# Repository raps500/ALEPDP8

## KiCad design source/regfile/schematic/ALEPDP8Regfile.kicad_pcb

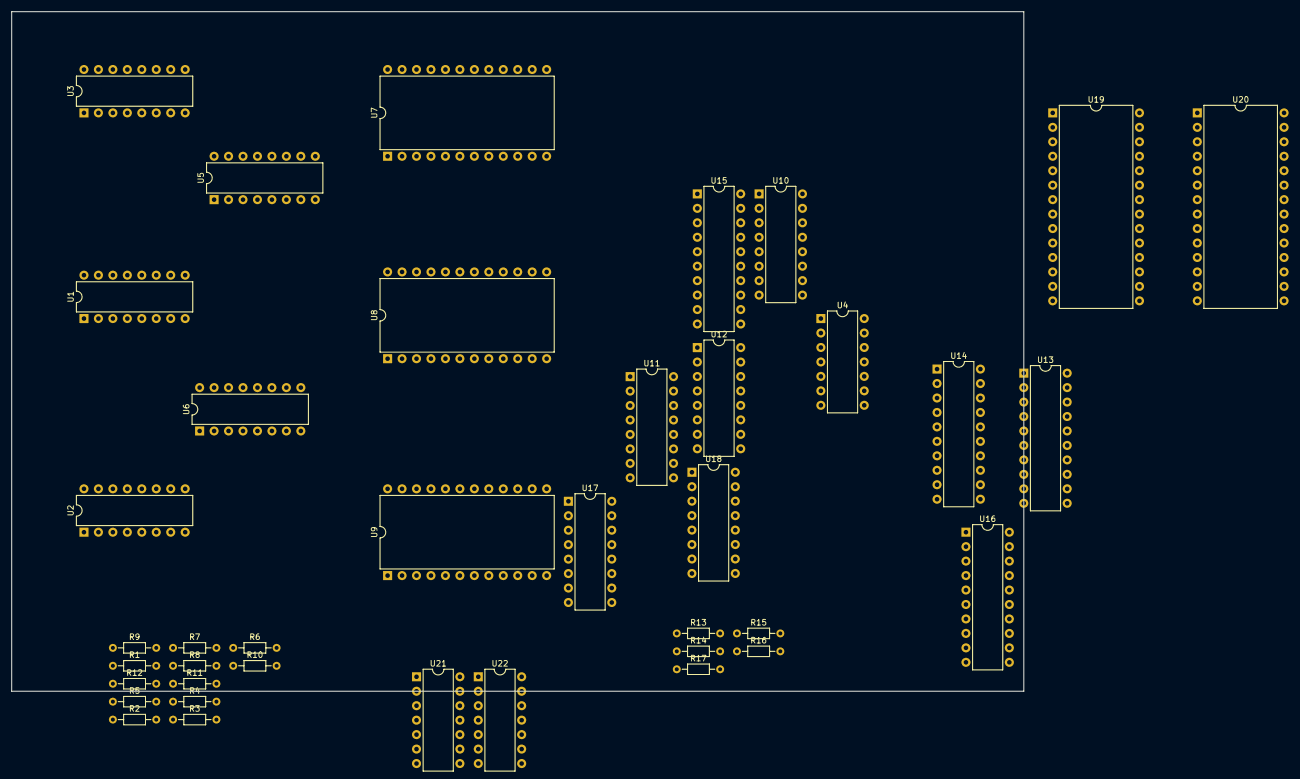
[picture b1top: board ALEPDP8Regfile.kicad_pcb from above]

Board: 2 copper layers, 177.8 x 119.4 mm, 39 parts (0 on the bottom side), 97 nets, no tracks yet.

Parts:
R1, R2, R3, R4, R5, R6, R7, R8, R9, R10, R11, R12, R13, R14, R15, R16, R17: 1 k; R_Axial_DIN0204_L3.6mm_D1.6mm_P7.62mm_Horizontal
U1, U2, U3: 74LS670; DIP-16_W7.62mm
U4, U21: 74LS125; DIP-14_W7.62mm
U5, U6, U17, U18: 74LS174; DIP-16_W7.62mm
U7, U8, U9: 74LS181; DIP-24_W15.24mm
U10, U11, U12: 74LS194; DIP-16_W7.62mm
U13: 74LS541; DIP-20_W7.62mm
U14, U15, U16: 74LS244; DIP-20_W7.62mm
U19, U20: CY62256-70PC; DIP-28_W15.24mm
U22: 74LS74; DIP-14_W7.62mm

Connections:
+5V: U1.16 (VCC), U2.16 (VCC), U3.16 (VCC), U5.16 (VCC), U6.16 (VCC), U7.24 (VCC), U8.24 (VCC), U9.24 (VCC), U10.16 (VCC), U11.16 (VCC), U12.16 (VCC), U14.20 (VCC), U15.20 (VCC), U16.20 (VCC), U17.1 (~Mr), U17.16 (VCC), U18.1 (~Mr), U18.16 (VCC), U19.28 (VCC), U20.28 (VCC)
/IBUS0: U3.15 (D1), U5.3 (D0), U13.18 (Y0), U14.2 (I0a), U14.11 (I0b), U17.3 (D0)
/IBUS1: U3.1 (D2), U5.4 (D1), U13.17 (Y1), U14.4 (I1a), U14.13 (I1b), U17.4 (D1)
/IBUS2: U3.2 (D3), U5.6 (D2), U13.16 (Y2), U14.6 (I2a), U14.15 (I2b), U17.6 (D2)
/IBUS3: U3.3 (D4), U5.11 (D3), U13.15 (Y3), U14.8 (I3a), U14.17 (I3b), U17.11 (D3)
/IBUS4: U1.15 (D1), U5.13 (D4), U13.14 (Y4), U15.2 (I0a), U15.11 (I0b), U17.13 (D4)
/IBUS5: U1.1 (D2), U5.14 (D5), U13.13 (Y5), U15.4 (I1a), U15.13 (I1b), U17.14 (D5)
/IBUS6: U1.2 (D3), U6.3 (D0), U13.12 (Y6), U15.6 (I2a), U15.15 (I2b)
/IBUS7: U1.3 (D4), U6.4 (D1), U13.11 (Y7), U15.8 (I3a), U15.17 (I3b), U21.12
/IBUS8: U2.15 (D1), U4.3, U6.6 (D2), U16.2 (I0a), U16.11 (I0b)
/IBUS9: U2.1 (D2), U4.6, U6.11 (D3), U16.4 (I1a), U16.13 (I1b)
/IBUS10: U2.2 (D3), U4.8, U6.13 (D4), U16.6 (I2a), U16.15 (I2b)
/IBUS11: U2.3 (D4), U4.11, U6.14 (D5), U16.8 (I3a), U16.17 (I3b)
GND: R1.2, R2.2, R3.2, R4.2, R5.2, R6.2, R7.2, R8.2, R9.2, R10.2, R11.2, R12.2, R13.2, R14.2, R15.2, R16.2, R17.2, U1.8 (GND), U2.8 (GND), U3.8 (GND), U5.8 (GND), U6.8 (GND), U7.12 (GND), U8.12 (GND), U9.12 (GND), U10.8 (GND), U11.8 (GND), U12.8 (GND), U14.10 (GND), U15.10 (GND), U16.10 (GND), U17.8 (GND), U18.8 (GND), U19.14 (GND), U20.14 (GND)
unnamed: R1.1, U3.6 (Q4), U7.19 (A3)
unnamed: R2.1, U2.6 (Q4), U9.19 (A3)
unnamed: R3.1, U1.6 (Q4), U8.19 (A3)
unnamed: R4.1, U3.7 (Q3), U7.21 (A2)
unnamed: R5.1, U2.7 (Q3), U9.21 (A2)
unnamed: R6.1, U1.7 (Q3), U8.21 (A2)
unnamed: R7.1, U3.9 (Q2), U7.23 (A1)
unnamed: R8.1, U2.9 (Q2), U9.23 (A1)
unnamed: R9.1, U1.9 (Q2), U8.23 (A1)
unnamed: R10.1, U3.10 (Q1), U7.2 (A0)
unnamed: R11.1, U2.10 (Q1), U9.2 (A0)
unnamed: R12.1, U1.10 (Q1), U8.2 (A0)
unnamed: U1.4 (Rb), U2.4 (Rb), U3.4 (Rb)
unnamed: U1.5 (Ra), U2.5 (Ra), U3.5 (Ra)
unnamed: U1.11 (~Er), U2.11 (~Er), U3.11 (~Er)
unnamed: U1.12 (~Ew), U2.12 (~Ew), U3.12 (~Ew)
unnamed: U1.13 (Wb), U2.13 (Wb), U3.13 (Wb)
unnamed: U1.14 (Wa), U2.14 (Wa), U3.14 (Wa)
unnamed: U5.2 (Q0), U7.1 (B0)
unnamed: U5.5 (Q1), U7.22 (B1)
unnamed: U5.7 (Q2), U7.20 (B2)
unnamed: U5.10 (Q3), U7.18 (B3)
unnamed: U5.12 (Q4), U8.1 (B0)
unnamed: U5.15 (Q5), U8.22 (B1)
unnamed: U6.2 (Q0), U8.20 (B2)
unnamed: U6.5 (Q1), U8.18 (B3)
unnamed: U6.7 (Q2), U9.1 (B0)
unnamed: U6.10 (Q3), U9.22 (B1)
unnamed: U6.12 (Q4), U9.20 (B2)
unnamed: U6.15 (Q5), U9.18 (B3)
unnamed: U7.3 (S3), U8.3 (S3), U9.3 (S3)
unnamed: U7.4 (S2), U8.4 (S2), U9.4 (S2)
unnamed: U7.5 (S1), U8.5 (S1), U9.5 (S1)
unnamed: U7.6 (S0), U8.6 (S0), U9.6 (S0)
unnamed: U7.8 (M), U8.8 (M), U9.8 (M)
unnamed: U7.16 (Cn+4), U8.7 (Cn)
unnamed: U8.16 (Cn+4), U9.7 (Cn)
unnamed: U7.9 (F0), U10.3 (P0)
unnamed: U7.10 (F1), U10.4 (P1)
unnamed: U7.11 (F2), U10.5 (P2)
unnamed: U7.13 (F3), U10.6 (P3)
unnamed: U10.12 (Q3), U11.7 (Dsl), U13.5 (A3)
unnamed: U10.13 (Q2), U13.4 (A2)
unnamed: U10.14 (Q1), U13.3 (A1)
unnamed: U10.15 (Q0), U13.2 (A0), U21.5
unnamed: U4.2, U11.2 (Dsr), U12.15 (Q0)
unnamed: U8.9 (F0), U11.3 (P0)
unnamed: U8.10 (F1), U11.4 (P1)
unnamed: U8.11 (F2), U11.5 (P2)
unnamed: U8.13 (F3), U11.6 (P3)
unnamed: U11.13 (Q2), U13.8 (A6)
unnamed: U11.14 (Q1), U13.7 (A5)
unnamed: U10.2 (Dsr), U11.15 (Q0), U13.6 (A4)
unnamed: U10.7 (Dsl), U12.2 (Dsr), U22.5 (Q)
unnamed: U9.9 (F0), U12.3 (P0)
unnamed: U9.10 (F1), U12.4 (P1)
unnamed: U9.11 (F2), U12.5 (P2)
unnamed: U9.13 (F3), U12.6 (P3)
unnamed: U11.12 (Q3), U12.7 (Dsl), U13.9 (A7)
unnamed: U4.12, U12.12 (Q3), U21.2
unnamed: U4.9, U12.13 (Q2)
unnamed: U4.5, U12.14 (Q1)
unnamed: U4.1, U4.4, U4.10, U4.13, U13.1 (G1), U13.19 (G2)
unnamed: U14.3 (O3b), U14.12 (O3a)
unnamed: U14.5 (O2b), U14.14 (O2a)
unnamed: U14.7 (O1b), U14.16 (O1a)
unnamed: U14.9 (O0b), U14.18 (O0a)
unnamed: U15.3 (O3b), U15.12 (O3a)
unnamed: U15.5 (O2b), U15.14 (O2a)
unnamed: U15.7 (O1b), U15.16 (O1a)
unnamed: U15.9 (O0b), U15.18 (O0a)
unnamed: U16.3 (O3b), U16.12 (O3a)
unnamed: U16.5 (O2b), U16.14 (O2a)
unnamed: U16.7 (O1b), U16.16 (O1a)
unnamed: U16.9 (O0b), U16.18 (O0a)
unnamed: U17.9 (Cp), U18.9 (Cp)
unnamed: R14.1, U18.4 (D1), U21.11
unnamed: R15.1, U18.6 (D2)
unnamed: R17.1, U18.11 (D3)
unnamed: R16.1, U18.13 (D4)
unnamed: R13.1, U18.14 (D5)
unnamed: U21.3, U21.6, U21.8, U22.2 (D)
unnamed: U21.9, U22.6 (~Q)

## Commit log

2023-03-18 Create .gitignore
    Added rule for GHDL
2023-03-18 Initial state
